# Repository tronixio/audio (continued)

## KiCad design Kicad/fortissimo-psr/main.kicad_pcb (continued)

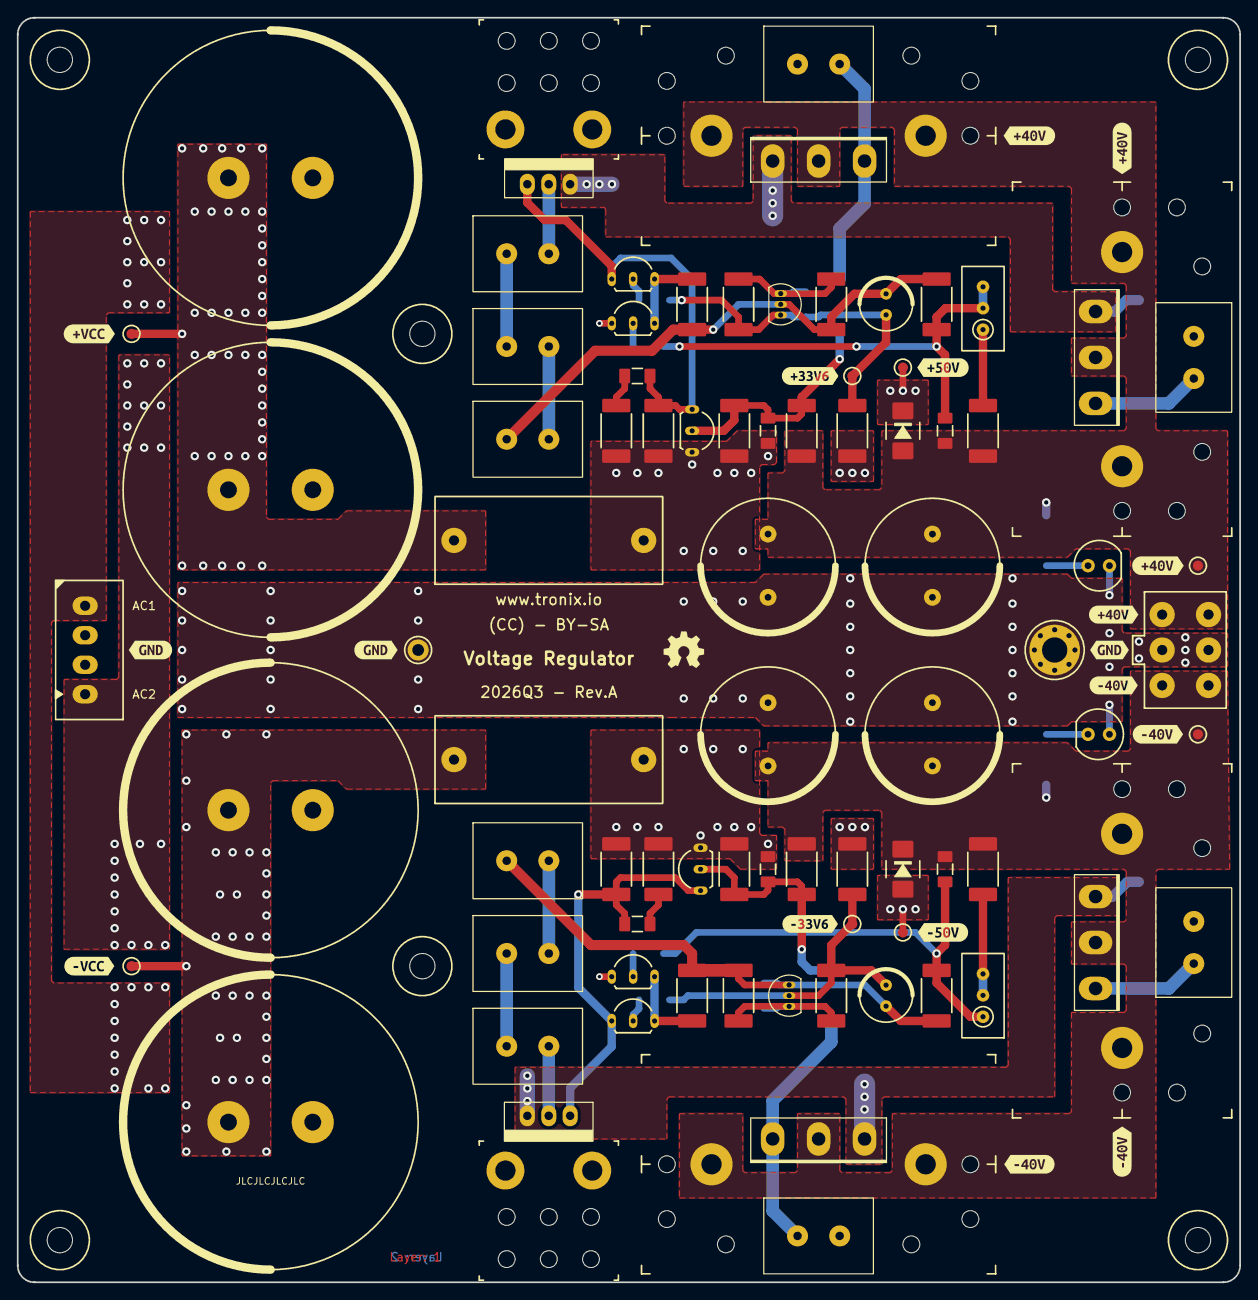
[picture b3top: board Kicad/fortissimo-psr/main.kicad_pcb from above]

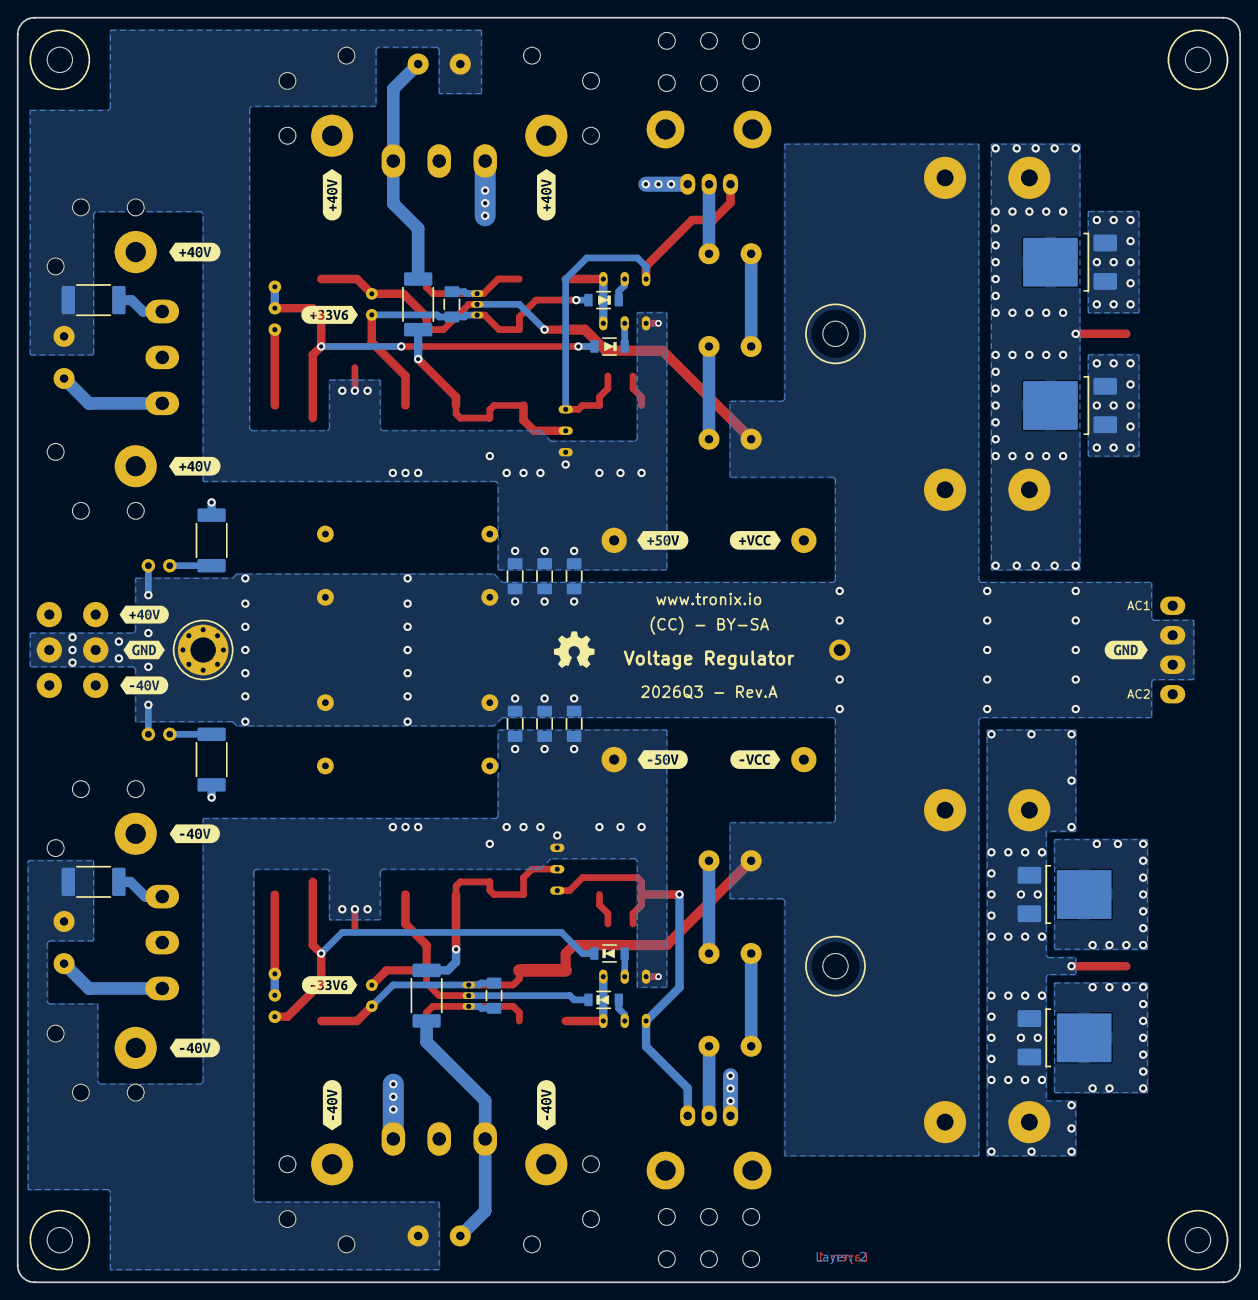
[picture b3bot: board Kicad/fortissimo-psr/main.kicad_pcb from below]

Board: 2 copper layers, 145.0 x 150.0 mm, 153 parts (40 on the bottom side), 43 nets.

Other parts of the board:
kibuzzard-6A91DFCB: G***; kibuzzard-6A91DFCB
kibuzzard-6A91DFE1: G***; kibuzzard-6A91DFE1
kibuzzard-6A553A81: G***; kibuzzard-6A553A81
kibuzzard-6A553AA5: G***; kibuzzard-6A553AA5
kibuzzard-6A553AF9: G***; kibuzzard-6A553AF9
kibuzzard-6A553B05, kibuzzard-6A553B05#2: G***; kibuzzard-6A553B05
kibuzzard-6A553B5A: G***; kibuzzard-6A553B5A
kibuzzard-6A553BDC: G***; kibuzzard-6A553BDC
kibuzzard-6A553C03, kibuzzard-6A553C03#2: G***; kibuzzard-6A553C03
kibuzzard-6A553D3F, kibuzzard-6A553D3F#2: G***; kibuzzard-6A553D3F
kibuzzard-6A553D94, kibuzzard-6A553D94#2: G***; kibuzzard-6A553D94
kibuzzard-6A553DC5, kibuzzard-6A553DC5#2: G***; kibuzzard-6A553DC5
kibuzzard-6A5620D1: G***; kibuzzard-6A5620D1
kibuzzard-6A554039: G***; kibuzzard-6A554039
kibuzzard-6A554067: G***; kibuzzard-6A554067
kibuzzard-6A554084: G***; kibuzzard-6A554084
kibuzzard-65E2F8A5: G***; kibuzzard-65E2F8A5
kibuzzard-65E2F8AC: G***; kibuzzard-65E2F8AC
kibuzzard-65E2F8D2: G***; kibuzzard-65E2F8D2
kibuzzard-65E2F8DA: G***; kibuzzard-65E2F8DA
kibuzzard-65E2F97B: G***; kibuzzard-65E2F97B
kibuzzard-65E2F965: G***; kibuzzard-65E2F965
kibuzzard-65E2FA94: G***; kibuzzard-65E2FA94
kibuzzard-65E2FABC: G***; kibuzzard-65E2FABC
kibuzzard-67B3A61B: G***; kibuzzard-67B3A61B
kibuzzard-67B3A610: G***; kibuzzard-67B3A610
kibuzzard-67B3AA9A: G***; kibuzzard-67B3AA9A
kibuzzard-67B3AA80: G***; kibuzzard-67B3AA80
kibuzzard-67B3AA87: G***; kibuzzard-67B3AA87
kibuzzard-67B3AA90: G***; kibuzzard-67B3AA90

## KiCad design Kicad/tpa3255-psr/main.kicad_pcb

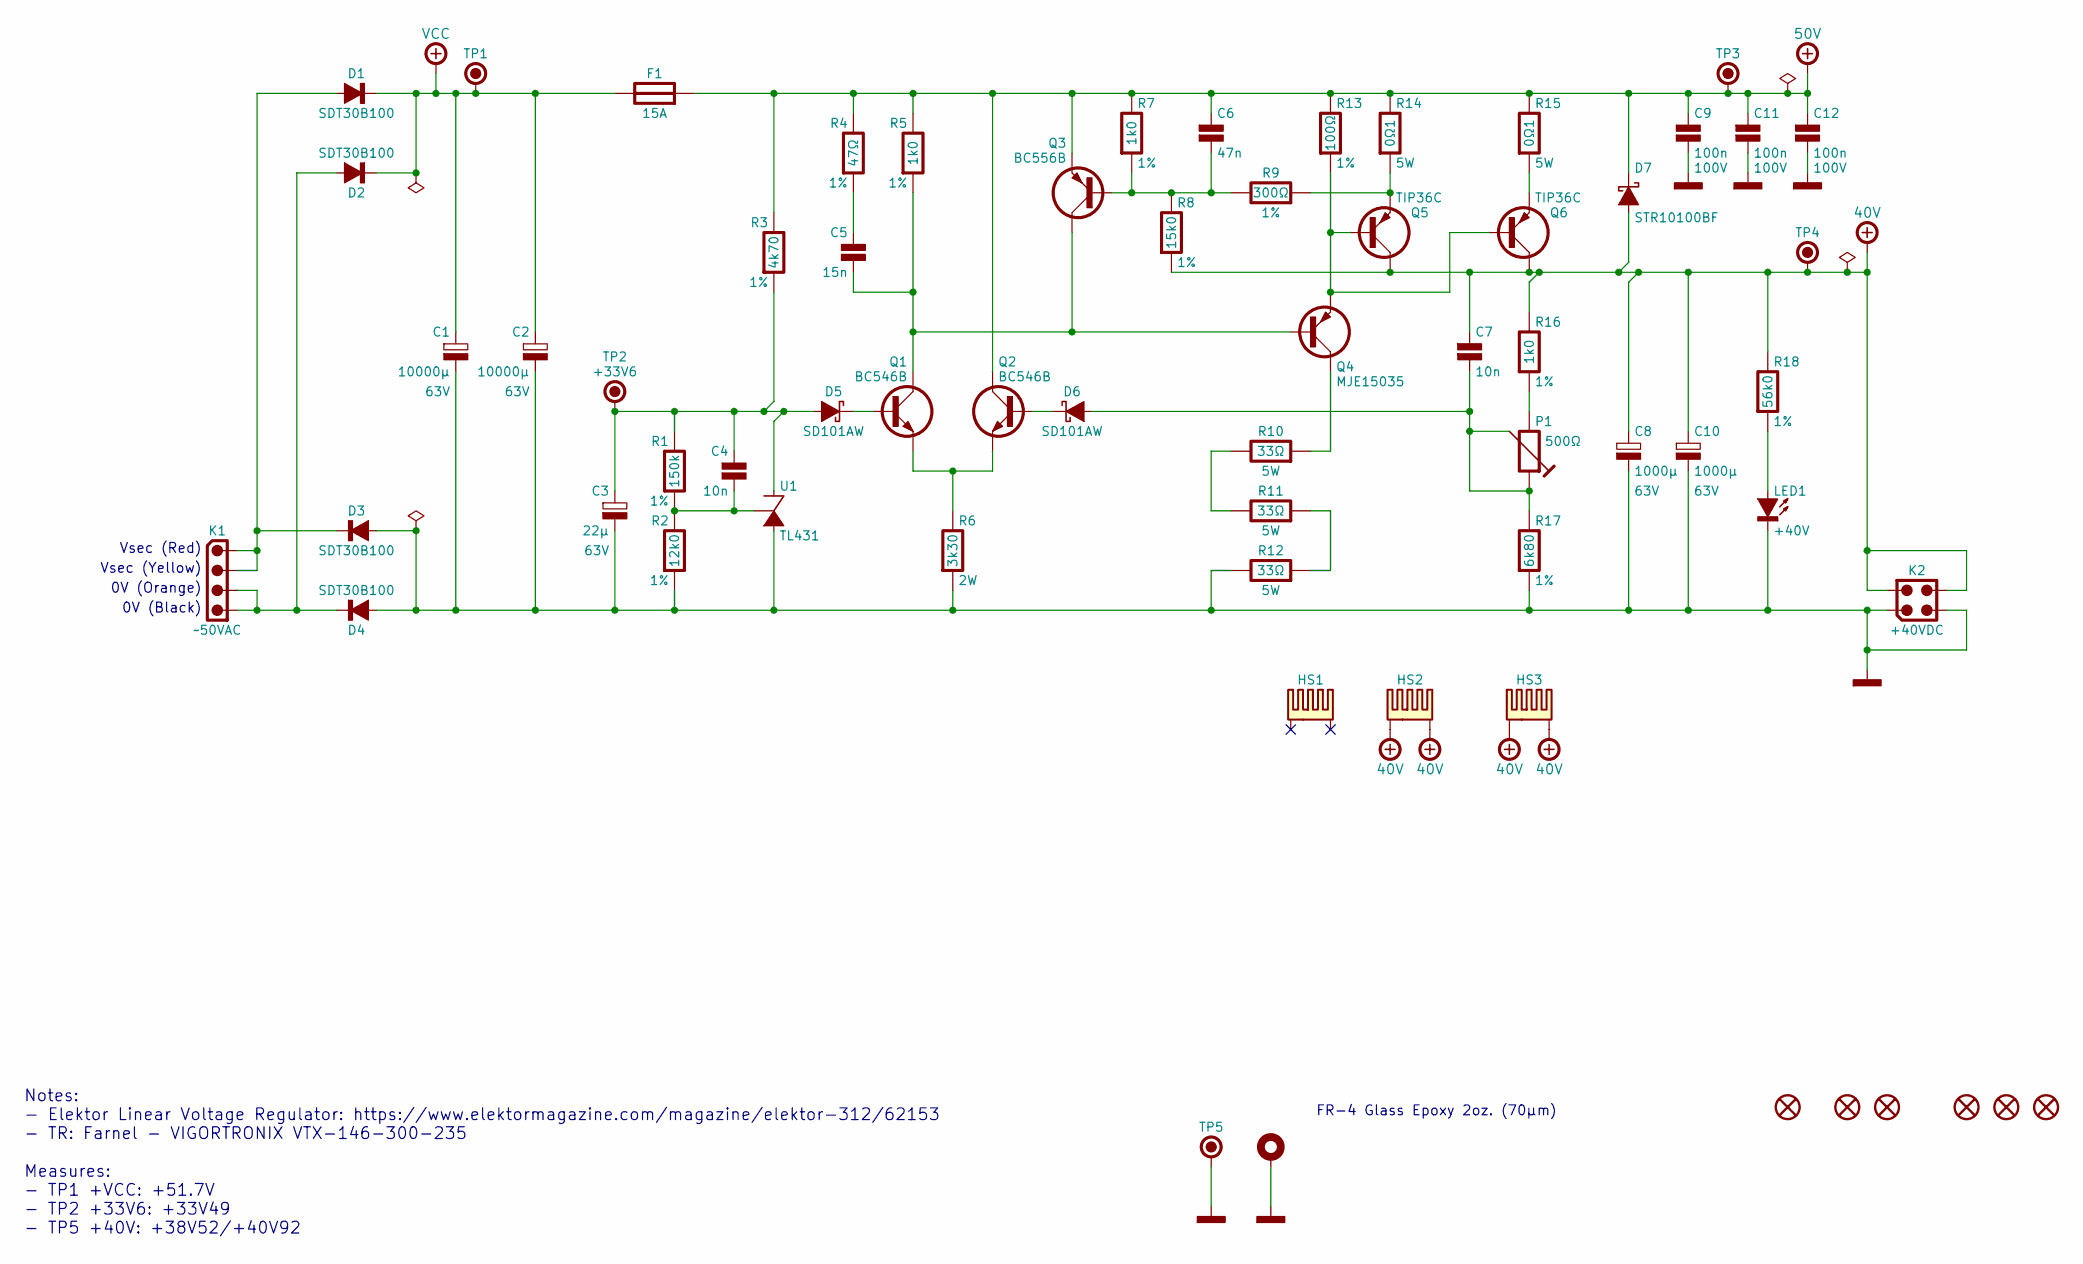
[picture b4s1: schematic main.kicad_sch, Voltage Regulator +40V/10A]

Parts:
C1, C2: 10000µ; CAPACITOR-ELECTROLYTIC-RADIAL-350-520-010-WURTH; Tolerance 20%; Voltage 63V; Mouser 710-861140786024
C3: 22µ; CAPACITOR-ELECTROLYTIC-RADIAL-063-110-025-WURTH; Voltage 63V; Tolerance 20%; Mouser 710-860080773004
C4, C7: 10n; CAPACITOR-SMD-1206; Voltage 100V; Tolerance 5%; Mouser 80-C1206C103J1R
C5: 15n; CAPACITOR-SMD-1206; Voltage 100V; Tolerance 5%; Mouser 80-C1206C153J1R
C6: 47n; CAPACITOR-SMD-1206; Tolerance 5%; Voltage 100V; Mouser 603-CC126JRX7R0BB473
C8, C10: 1000µ; CAPACITOR-ELECTROLYTIC-RADIAL-160-250-075-WURTH; Tolerance 20%; Voltage 63V; Mouser 661-EKYB630E102ML25S
C9, C11, C12: 100n; CAPACITOR-SMD-1206; Tolerance 5%; Voltage 100V; Mouser 80-C1206C104J1R7210
D1, D2, D3, D4: SDT30B100; TO-252-2; Mouser 621-SDT30B100D1-13
D5, D6: SD101AW; SOD-123; Part Marking S1/SK; Mouser 621-SD101AW-F
D7: STR10100BF; DIODE-SMBF; Mouser 241-STR10100BFR10701
F1: 15A; SCHURTER-OGN-3132874; Mouser 693-3-132-874
F2: 15A; FUSE-CARTRIDGE-5X20; Mouser 576-0215015.MXP
H1: GND; MOUNTING-HOLE-3MM-PAD-VIA
HS1: HSE19-361616P; SAMESKY-HSE19-361616P; Mouser 179-HSE19-361616P
HS2, HS3: WAKEFIELD-657-25ABEP; Mouser 567-657-25ABEP
K1: ~50VAC; MOLEX-532580429; Mouser 538-53258-0429
K2: +40VDC; MOLEX-39281043; Mouser 538-39-28-1043
K3: MIGHTY-SPOX; MOLEX-510670400; Mouser 538-51067-0400 / 538-50217-8000-CT / 53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
K4: MINI-FIT; MOLEX-39012040; Mouser 538-39-01-2040 / 538-39-00-0039 / 538-3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
LED1: +40V; LED-TH-ROUND-05MM; Mouser 593-VAOL-5LSBY1
MH1, MH2, MH3: MOUNTING-HOLE-3MM-MASK
P1: 500Ω; TRIMMER-64W; Tolerance 10%; Mouser 858-67WR500LF
Q1, Q2: BC546B; TO-92-INLINE-WIDE; Mouser 512-BC546BTF
Q3: BC556B; TO-92-INLINE-WIDE; Mouser 512-BC556BTF
Q4: MJE15035; TO-220-3-VERTICAL; Mouser 863-MJE15035G
Q5, Q6: TIP36C; TO-247-3-VERTICAL; Mouser 511-TIP36C
R1: 150k; RESISTOR-SMD-2512; Tolerance 1%; Mouser 603-RC2512FK-07150KL
R2: 12k0; RESISTOR-SMD-2512; Tolerance 1%; Mouser 603-RC2512FK-0712KL
R3: 4k70; RESISTOR-SMD-2512; Tolerance 1%; Mouser 603-RC2512FK-074K7L
R4: 47Ω; RESISTOR-SMD-2512; Tolerance 1%; Mouser 603-RC2512FK-0747RL
R5, R7, R16: 1k0; RESISTOR-SMD-2512; Tolerance 1%; Mouser 603-RC2512FK-071KL
R6: 3k30; RESISTOR-SMD-2512; Tolerance 5%; Mouser 279-CRGH2512J3K3
R8: 15k0; RESISTOR-SMD-2512; Tolerance 1%; Mouser 603-RC2512FK-0715KL
R9: 300Ω; RESISTOR-SMD-2512; Tolerance 1%; Mouser 603-RC2512FK-07300RL
R10, R11, R12: 33Ω; TE-SQM-130-090-250-050; Tolerance 5%; Mouser 279-SQMW533RJ
R13: 100Ω; RESISTOR-SMD-2512; Tolerance 1%; Mouser 603-RC2512FK-07100RL
R14, R15: 0Ω1; TE-SQM-130-090-250-050; Tolerance 5%; Mouser 279-SQMW5R10J
R17: 6k80; RESISTOR-SMD-2512; Tolerance 1%; Mouser 603-RC2512FK-076K8L
R18: 56k0; RESISTOR-SMD-2512; Tolerance 1%; Mouser 603-RC2512FK-0756KL
TP1: +VCC; TRONIXIO-TP
TP2: +33V6; TRONIXIO-TP
TP3: +50V; TRONIXIO-TP
TP4: +40V; TRONIXIO-TP
TP5: GND; KEYSTONE-5006; Mouser 534-5006
U1: TL431; TO-92-INLINE; Mouser 863-TL431BCLPG

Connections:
+40V: C7.1, C8.1, C10.1, D7.2 (A), HS2.1, HS2.2, HS3.1, HS3.2, K2.2, K2.4, Q5.2 (C), Q6.2 (C), R8.2, R16.1, R18.1, TP4.1
+50V: C6.1, C9.1, C11.1, C12.1, D7.1 (C), F1.2, Q2.1 (C), Q3.3 (E), R3.1, R4.1, R5.1, R7.1, R13.1, R14.1, R15.1, TP3.1
+VCC: C1.1, C2.1, D1.2 (C), D2.2 (C), F1.1, TP1.1
GND: C1.2, C2.2, C3.2, C8.2, C9.2, C10.2, C11.2, C12.2, D3.1 (A), D3.3 (A), D4.1 (A), D4.3 (A), H1.1, K2.1, K2.3, LED1.1 (C), R2.2, R6.2, R12.1, R17.2, TP5.1, U1.2 (A)
unnamed: C5.1, R4.2
unnamed: D1.1 (A), D1.3 (A), D3.2 (C), K1.1, K1.2
unnamed: D2.1 (A), D2.3 (A), D4.2 (C), K1.3, K1.4
unnamed: C3.1, C4.1, D5.2 (A), R1.1, R3.2, TP2.1, U1.3 (C)
unnamed: D5.1 (C), Q1.2 (B)
unnamed: C7.2, D6.2 (A), P1.2, P1.3, R17.1
unnamed: D6.1 (C), Q2.2 (B)
unnamed: LED1.2 (A), R18.2
unnamed: P1.1, R16.2
unnamed: C5.2, Q1.1 (C), Q3.1 (C), Q4.1 (B), R5.2
unnamed: Q1.3 (E), Q2.3 (E), R6.1
unnamed: C6.2, Q3.2 (B), R7.2, R8.1, R9.1
unnamed: Q4.2 (C), R10.2
unnamed: Q4.3 (E), Q5.1 (B), Q6.1 (B), R13.2
unnamed: Q5.3 (E), R9.2, R14.2
unnamed: Q6.3 (E), R15.2
unnamed: R10.1, R11.1
unnamed: R11.2, R12.2
unnamed: C4.2, R1.2, R2.1, U1.1 (R)

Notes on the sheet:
FR-4 Glass Epoxy 2oz. (70µm)
Vsec (Red)
0V (Orange)
0V (Black)
Notes: - Elektor Linear Voltage Regulator: https://www.elektormagazine.com/magazine/elektor-312/62153 - TR: Farnel - VIGORTRONIX VTX-146-300-235 Measures: - TP1 +VCC: +51.7V - TP2 +33V6: +33V49 - TP5 +40V: +38V52/+40V92
Vsec (Yellow)

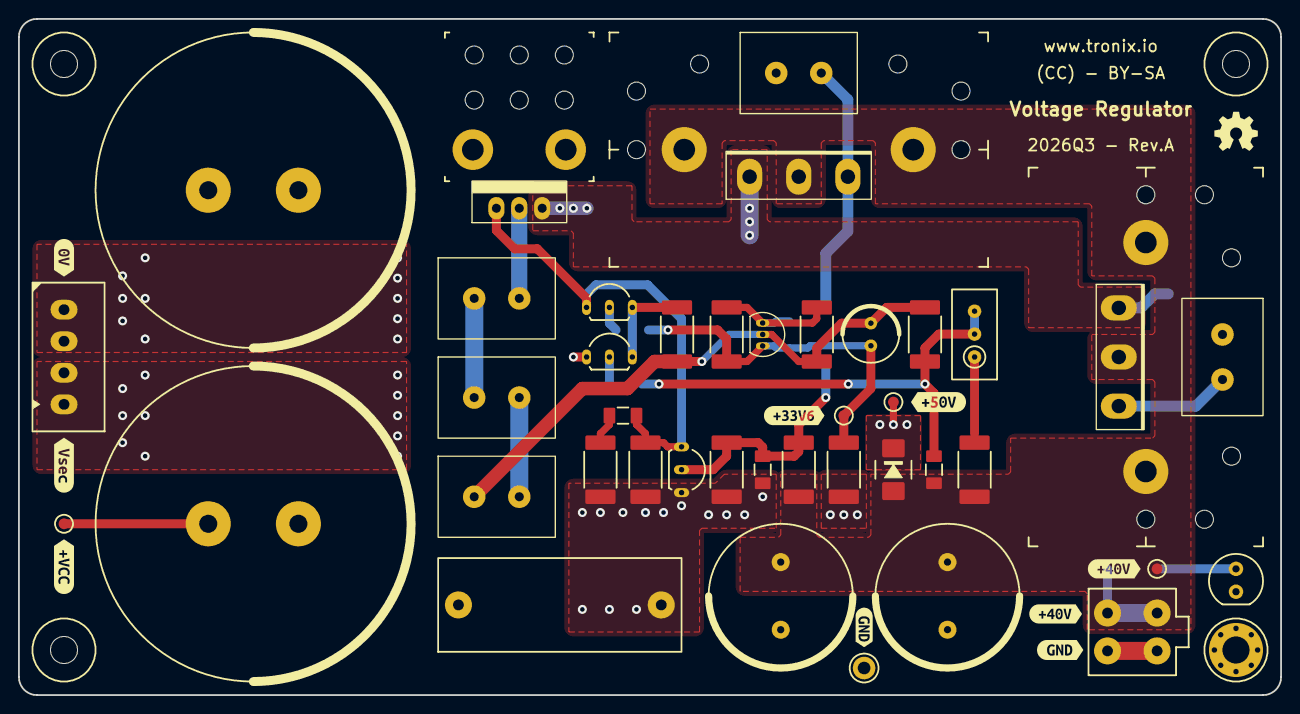
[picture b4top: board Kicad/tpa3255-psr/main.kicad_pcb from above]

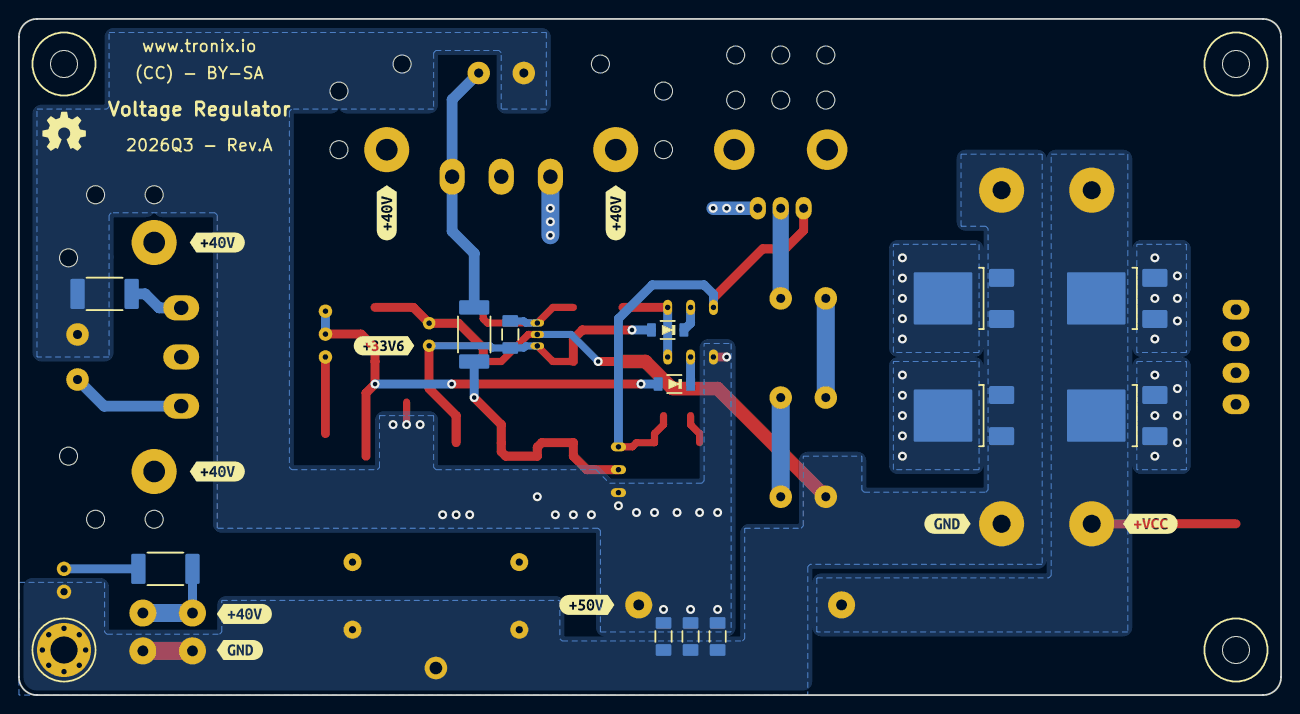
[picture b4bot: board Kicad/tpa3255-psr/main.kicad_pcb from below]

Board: 2 copper layers, 140.0 x 75.0 mm, 83 parts (23 on the bottom side), 23 nets.

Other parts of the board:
kibuzzard-6A91E76A: G***; kibuzzard-6A91E76A
kibuzzard-6A91E653, kibuzzard-6A91E653#2: G***; kibuzzard-6A91E653
kibuzzard-6A91E771: G***; kibuzzard-6A91E771
kibuzzard-6A553AA5: G***; kibuzzard-6A553AA5
kibuzzard-6A807B1E: G***; kibuzzard-6A807B1E
kibuzzard-6A807B5B, kibuzzard-6A807B5B#2: G***; kibuzzard-6A807B5B
kibuzzard-6A807C3A: G***; kibuzzard-6A807C3A
kibuzzard-6A808BC1: G***; kibuzzard-6A808BC1
kibuzzard-6A808C25: G***; kibuzzard-6A808C25
kibuzzard-6A808C32: G***; kibuzzard-6A808C32
kibuzzard-6A808E0F: G***; kibuzzard-6A808E0F
kibuzzard-6A9090E6: G***; kibuzzard-6A9090E6
kibuzzard-6A9090F4: G***; kibuzzard-6A9090F4
kibuzzard-65E2F8A5, kibuzzard-65E2F8A5#2: G***; kibuzzard-65E2F8A5
kibuzzard-65E2F8D2: G***; kibuzzard-65E2F8D2
kibuzzard-65E2FA94: G***; kibuzzard-65E2FA94

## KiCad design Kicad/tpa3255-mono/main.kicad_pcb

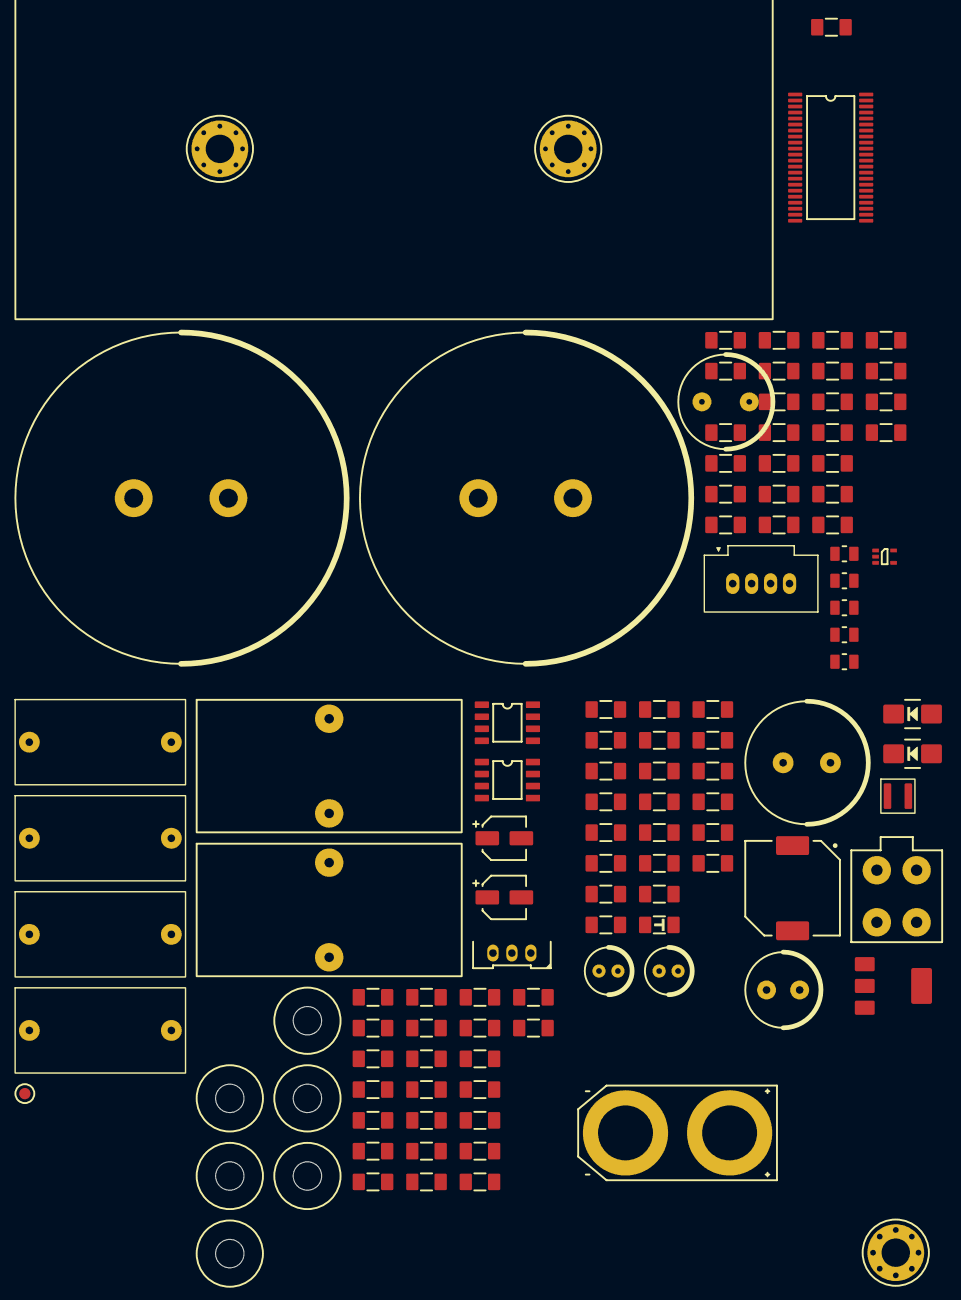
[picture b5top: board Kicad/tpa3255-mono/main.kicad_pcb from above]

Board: 2 copper layers, 115 parts (0 on the bottom side), 51 nets, no tracks yet.

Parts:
C101, C102, C117, C118: 220p; CAPACITOR-SMD-1206
C103, C114, C218: 10µ; CAPACITOR-SMD-1206
C104, C115: 10µ; CAPACITOR-ELECTROLYTIC-SMD-040-055-WURTH
C105, C113, C205: 10n; CAPACITOR-SMD-1206
C106, C107, C110, C111: 470n; WIMA-FILM-CAPACITOR-RADIAL-180-090-160-150
C108, C112: 1n; CAPACITOR-SMD-1206
C109, C116: 22p; CAPACITOR-SMD-1206
C201, C309: 47n; CAPACITOR-SMD-1206
C202: 5n6; CAPACITOR-SMD-1206
C203: 47µ; CAPACITOR-ELECTROLYTIC-RADIAL-130-200-050-WURTH
C204, C310, C311, C312, C313, C314, C316, C317, C321, C322: 1µ; CAPACITOR-SMD-1206
C206: 2µ2; CAPACITOR-SMD-1206
C207, C209, C213, C214, C216, C219, C308, C319, C320, C323: 100n; CAPACITOR-SMD-1206
C208: 4n7; CAPACITOR-SMD-1206
C210: 4µ7; CAPACITOR-SMD-1206
C211: 470n; CAPACITOR-SMD-1206
C212: 47µ; CAPACITOR-ELECTROLYTIC-RADIAL-080-115-035-WURTH
C215, C217: 10µ; CAPACITOR-ELECTROLYTIC-RADIAL-050-110-020-WURTH
C301, C302, C303, C304: 33n; CAPACITOR-SMD-0805
C305, C306: 100p; CAPACITOR-SMD-1206
C307: 470µ; CAPACITOR-ELECTROLYTIC-RADIAL-100-160-050-WURTH
C315, C318: 4700µ; CDE-SLPX-350-400-010
D201: SL310A; DIODE-SMA
D202: B1100; DIODE-SMA
H101: MOUNTING-HOLE-3MM-PAD-VIA
HS301: ATS-TI10P-519-C1-R3
K101: ANALOG IN; MOLEX-532530370
K102: HP; XT90H-FEMALE
K103: MOLEX-MINI-FIT; MOLEX-39012040
K201: +50V; MOLEX-39281043
K301: MCU; MOLEX-559320430
L101, L102: 10µH; COILCRAFT-MA5172
L201: 100µH; INDUCTOR-SMD-100-100-050
L202: 10µH; INDUCTOR-SMD-1212
L301: 10µH; INDUCTOR-SMD-0805
LED201: Power; LED-SMD-1206
MH101, MH102, MH103, MH104, MH105, MH106: MOUNTING-HOLE-3MM-MASK
R101, R110: 33k0; RESISTOR-SMD-1206
R102, R103, R104, R108, R109, R111, R204, R206: 10k0; RESISTOR-SMD-1206
R105, R107, R301, R302: 3Ω3; RESISTOR-SMD-1206
R106, R307: 100k; RESISTOR-SMD-1206
R201: 182k; RESISTOR-SMD-1206
R202: 4k99; RESISTOR-SMD-1206
R203: 1k0; RESISTOR-SMD-1206
R205: 30k; RESISTOR-SMD-1206
R303, R304: 100Ω; RESISTOR-SMD-1206
R305: 22k0; RESISTOR-SMD-1206
R306: 30k0; RESISTOR-SMD-1206
R308: 9k10; RESISTOR-SMD-1206
R309: 3k30; RESISTOR-SMD-1206
TP101: SYMBOL-TP; TRONIXIO-TP
U101, U102: OPA134; SOIC-08
U103: XT90H-M; XT90H-MALE
U202: LM2940-12; SOT-223-3-TABPIN2
U301: TPA3255; HTSSOP-44
U302: TPS3802K33; SC-70-5
kibuzzard-62A777FA: G***; kibuzzard-62A777FA

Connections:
+12V: C212.1, C213.1, L202.2, L301.2, R205.1, R301.1, R302.1, U202.3 (VOUT)
+12VA: C214.1, C215.1, C216.1, C217.1, L202.1, R204.1, U101.7 (V+), U102.7 (V+)
+15V: C210.1, C211.1, R308.1, U202.1 (VIN)
+50V: C203.1, C204.1, C205.1, C206.1, C207.1, C313.1, C314.1, C315.1, C316.1, C317.1, C318.1, D201.2 (A), K201.1, K201.3, R307.1, U301.29 (PVDD_CD), U301.30 (PVDD_CD), U301.31 (PVDD_CD), U301.36 (PVDD_AB), U301.37 (PVDD_AB), U301.38 (PVDD_AB)
+VBIAS: C218.1, C219.1, R204.2, R206.1, U101.3 (+), U102.3 (+)
/TPA3255/INPUT A: C103.1, R303.1
/TPA3255/INPUT B: C114.1, R304.1
/TPA3255/OUTPUT AC: C301.2, C302.2, L101.1, U301.32 (OUT_C), U301.39 (OUT_A), U301.40 (OUT_A)
/TPA3255/OUTPUT BD: C303.2, C304.2, L102.2, U301.27 (OUT_D), U301.28 (OUT_D), U301.35 (OUT_B)
GND: C106.2, C107.2, C108.2, C110.1, C111.1, C112.1, C203.2, C204.2, C205.2, C210.2, C211.2, C212.2, C213.2, C214.2, C215.2, C216.2, C217.2, C218.2, C219.2, C305.2, C306.2, C307.2, C308.2, C309.2, C310.2, C311.2, C312.2, C313.2, C314.2, C315.2, C316.2, C317.2, C318.2, C319.2, C320.2, C322.2, C323.2, H101.1, HS301.1, K101.2, K201.2, K201.4, K301.4, LED201.1 (C), R102.1, R105.2, R107.1, R111.1, R206.2, R305.2, R306.2, R309.2, TP101.1, U101.4 (V-), U102.4 (V-), U202.2 (GND), U301.3 (M1), U301.12 (GND), U301.13 (GND), U301.16 (INPUT_C), U301.17 (INPUT_D), U301.25 (GND), U301.26 (GND), U301.33 (GND), U301.34 (GND), U301.41 (GND), U301.42 (GND), U302.1 (GND), U302.2 (GND)
unnamed: C101.1, C103.2, C109.2, R101.1, R104.2, U101.6
unnamed: C101.2, C102.1, R102.2
unnamed: C104.1, R103.1
unnamed: C104.2, K101.1, R106.1
unnamed: C105.2, R105.1
unnamed: C113.1, R107.2
unnamed: C114.2, C116.2, C117.1, R109.2, R110.1, U102.6
unnamed: C115.1, R108.1
unnamed: C115.2, K101.3, R106.2
unnamed: C117.2, C118.1, R111.2
unnamed: C321.1, R307.2
unnamed: D201.1 (C), R201.1
unnamed: C201.2, D202.1 (C), L201.1
unnamed: C102.2, C105.1, C106.1, C107.1, C108.1, K102.2 (+), L101.2, R101.2
unnamed: C110.2, C111.2, C112.2, C113.2, C118.2, K102.1 (-), L102.1, R110.2
unnamed: LED201.2 (A), R205.2
unnamed: C109.1, R103.2, R104.1, U101.2 (-)
unnamed: C116.1, R108.2, R109.1, U102.2 (-)
unnamed: C202.2, R202.2, R203.1
unnamed: C311.1, U301.14 (AVDD)
unnamed: C301.1, U301.44 (BST_A)
unnamed: C303.1, U301.43 (BST_B)
unnamed: C302.1, U301.24 (BST_C)
unnamed: C304.1, U301.23 (BST_D)
unnamed: C309.1, U301.15 (C_START)
unnamed: C310.1, U301.4 (M2), U301.11 (DVDD)
unnamed: R306.1, U301.8 (FREQ_ADJ)
unnamed: C319.1, R301.2, U301.1 (GVDD_AB)
unnamed: C320.1, R302.2, U301.22 (GVDD_CD)
unnamed: C306.1, R303.2, U301.5 (INPUT_A)
unnamed: C305.1, R304.2, U301.6 (INPUT_B)
unnamed: R305.1, U301.7 (OC_ADJ)
unnamed: C312.1, U301.20 (VBG)
unnamed: C307.1, C308.1, L301.1, U301.2 (VDD)
unnamed: K301.2, U301.21 (~CLIP_OTW)
unnamed: K301.3, U301.19 (~FAULT)
unnamed: C321.2, C322.1, C323.1, R308.2, R309.1, U302.4 (VDD)
POWER-+15V: C202.1, L201.2, R202.1
POWER-GND: C206.2, C207.2, C208.2, C209.2, R203.2
~MCU RESET: K301.1, U302.5 (~MR)
~RESET: U301.18 (~RESET), U302.3 (~RESET)

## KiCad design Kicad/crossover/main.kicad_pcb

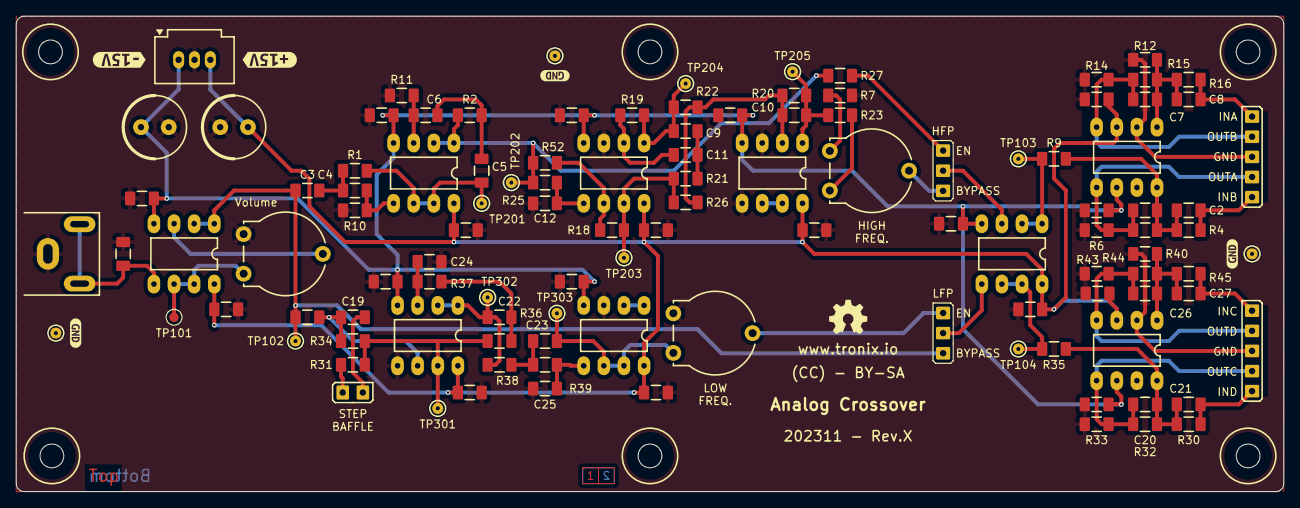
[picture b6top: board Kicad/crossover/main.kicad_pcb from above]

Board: 2 copper layers, 160.0 x 60.0 mm, 125 parts (0 on the bottom side), 54 nets.

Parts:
C1, C7, C20, C26: 220p; CAPACITOR-SMD-1206
C2, C8, C21, C27: 180p; CAPACITOR-SMD-1206
C3, C4, C5, C6, C9, C11, C12, C19, C22, C23, C101, C102, C103, C104, C106, C107, C115, C116, C201, C202, C203, C204, C205, C206, C305, C306, C307, C308: 100n; CAPACITOR-SMD-1206
C10: 10p; CAPACITOR-SMD-1206
C24, C25: 47n; CAPACITOR-SMD-1206
C105, C108: 220µ; CAPACITOR-ELECTROLYTIC-RADIAL-080-115-035-WURTH
H101, H102, H103, H104, H105, H106: MOUNTING-HOLE-3MM-MASK
JP6: Step Baffle; HARWIN-M20-999024x
K1: DELAY; HARWIN-M20-999034x
K5: LPF; HARWIN-M20-999034x
K101: INPUT; SWITCHCRAFT-PJRAN1X1U
K102: OUTPUT AB; HARWIN-M20-999054x
K104: OUTPUT CD; HARWIN-M20-999054x
K106: 15V; MOLEX-559320330
R1, R2: 3k57; RESISTOR-SMD-1206
R4, R16, R30, R45: 7k50; RESISTOR-SMD-1206
R5, R9, R12, R15, R18, R20, R23, R26, R27, R32, R35, R40, R44, R52: 1k00; RESISTOR-SMD-1206
R6, R14, R33, R43: 100k; RESISTOR-SMD-1206
R7, R28, R31, R34: 11k8; RESISTOR-SMD-1206
R8: 10k0; RESISTOR-SMD-1206
R10, R11: 7k87; RESISTOR-SMD-1206
R17: 20k; PIHER-PT10LV
R19: 422Ω; RESISTOR-SMD-1206
R21: 221Ω; RESISTOR-SMD-1206
R22: 475Ω; RESISTOR-SMD-1206
R24: 1k; PIHER-PT10LV
R25: 332Ω; RESISTOR-SMD-1206
R36, R38: 3k01; RESISTOR-SMD-1206
R37, R39: 4k99; RESISTOR-SMD-1206
R42: 10k; PIHER-PT10LV
TP101: SYMBOL-TP; TRONIXIO-TP
TP102, TP103, TP104, TP201, TP202, TP203, TP204, TP205, TP301, TP302, TP303: SYMBOL-TP; KEYSTONE-2000-3
TP105, TP106, TP107: KEYSTONE-2000-3
U4, U9: OPA1632; DIP-08-W762-SOCKET
U101, U102, U201, U202, U203, U301, U302: NE5532; DIP-08-W762-SOCKET
kibuzzard-62A777FA, kibuzzard-62A777FA#2, kibuzzard-62A777FA#3: G***; kibuzzard-62A777FA
kibuzzard-65509C73: G***; kibuzzard-65509C73
kibuzzard-65509CA4: G***; kibuzzard-65509CA4

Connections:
+15V: C101.2, C103.2, C105.1, C106.2, C115.2, C201.2, C203.2, C205.2, C305.2, C307.2, K106.3, U4.3 (V+), U9.3 (V+), U101.8 (VDD+), U102.8 (VDD+), U201.8 (VDD+), U202.8 (VDD+), U203.8 (VDD+), U301.8 (VDD+), U302.8 (VDD+)
-15V: C102.1, C104.1, C107.2, C108.2, C116.2, C202.1, C204.1, C206.1, C306.1, C308.1, K106.1, U4.6 (V-), U9.6 (V-), U101.4 (VDD-), U102.4 (VDD-), U201.4 (VDD-), U202.4 (VDD-), U203.4 (VDD-), U301.4 (VDD-), U302.4 (VDD-)
/High Pass Filter/input_all_pass_filter: C3.1, K5.3, R28.1, TP102.1, U101.1, U101.2 (-)
/High Pass Filter/output_all_pass_filter: K1.3, R24.2
/High Pass Filter/output_high_pass_filter: K1.1, R7.2
/Low Pass Filter/output_low_pass_filter: K5.1, R42.2
AMP-INA: C8.1, K102.1, R16.1
AMP-INB: C2.1, K102.5, R4.1
AMP-INC: C27.1, K104.1, R45.1
AMP-IND: C21.1, K104.5, R30.1
GND: C24.1, C25.1, C101.1, C102.2, C103.1, C104.2, C105.2, C106.1, C107.1, C108.1, C115.1, C116.1, C201.1, C202.2, C203.1, C204.2, C205.1, C206.2, C305.1, C306.2, C307.1, C308.2, K101.1, K102.3, K104.3, K106.2, R6.1, R8.1, R10.1, R11.1, R12.1, R14.1, R17.1, R25.2, R27.1, R33.1, R40.1, R42.1, R43.1, TP105.1, TP106.1, TP107.1, U4.2 (VOCM), U9.2 (VOCM), U202.3 (+), U203.3 (+), U203.5 (+), U301.5 (+), U302.3 (+)
unnamed: C3.2, C4.1, R1.1
unnamed: C5.2, C6.1, R2.1
unnamed: C9.2, R19.2, R22.1, TP204.1, U202.1
unnamed: C10.2, R20.2, R23.1, TP205.1, U203.1
unnamed: C9.1, C11.1, R21.2
unnamed: C19.2, JP6.1
unnamed: C22.1, R36.2, R37.1
unnamed: C23.1, R38.2, R39.1
unnamed: JP6.2, R31.1
unnamed: R18.2, R21.1, R26.1, TP203.1, U202.7
unnamed: R23.2, R24.3
unnamed: R24.1, R27.2
unnamed: R31.2, R34.2, R36.1, TP301.1, U301.7
unnamed: C1.1, C2.2, R4.2, R5.1, R9.2, U4.8 (VIN+)
unnamed: C7.1, C8.2, R12.2, R15.1, R16.2, U4.1 (VIN-)
unnamed: C7.2, K102.2, R14.2, R15.2, U4.4 (VOUT+)
unnamed: C1.2, K102.4, R5.2, R6.2, U4.5 (VOUT-)
unnamed: C20.1, C21.2, R30.2, R32.1, R35.2, U9.8 (VIN+)
unnamed: C26.1, C27.2, R40.2, R44.1, R45.2, U9.1 (VIN-)
unnamed: C26.2, K104.2, R43.2, R44.2, U9.4 (VOUT+)
unnamed: C20.2, K104.4, R32.2, R33.2, U9.5 (VOUT-)
unnamed: R17.2, U101.3 (+)
unnamed: K101.2, R8.2, U101.5 (+)
unnamed: R17.3, TP101.1, U101.6 (-), U101.7
unnamed: K1.2, U102.3 (+)
unnamed: R9.1, TP103.1, U102.1, U102.2 (-)
unnamed: K5.2, U102.5 (+)
unnamed: R35.1, TP104.1, U102.6 (-), U102.7
unnamed: C6.2, R11.2, U201.3 (+)
unnamed: C12.1, R2.2, R7.1, R52.1, TP202.1, U201.1, U201.2 (-)
unnamed: C4.2, R10.2, U201.5 (+)
unnamed: C5.1, R1.2, TP201.1, U201.6 (-), U201.7
unnamed: C11.2, R19.1, U202.2 (-)
unnamed: C12.2, R25.1, U202.5 (+)
unnamed: R18.1, R52.2, U202.6 (-)
unnamed: C10.1, R20.1, R22.2, R26.2, U203.2 (-)
unnamed: U203.6 (-), U203.7
unnamed: C24.2, R37.2, U301.3 (+)
unnamed: C22.2, R38.1, TP302.1, U301.1, U301.2 (-)
unnamed: C19.1, R28.2, R34.1, U301.6 (-)
unnamed: U302.1, U302.2 (-)
unnamed: C25.2, R39.2, U302.5 (+)
unnamed: C23.2, R42.3, TP303.1, U302.6 (-), U302.7
